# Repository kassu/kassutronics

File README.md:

# kassutronics
Under the label _kassutronics_ I create original circuits for modular musical synthesizers and other do-it-yourself sound electronics projects. Some of these are available for sale as printed circuit boards and face plates, others are only circuits or instructions.

This repository contains build documentation for modules that are for sale, and some smaller projects/workshops that are available as open source material.

## See also
- [Kassutronics blog](https://kassu2000.blogspot.com)
- [Kassutronics store](https://store.kassutronics.net)

- Added a new line just for testing the collaborative feature

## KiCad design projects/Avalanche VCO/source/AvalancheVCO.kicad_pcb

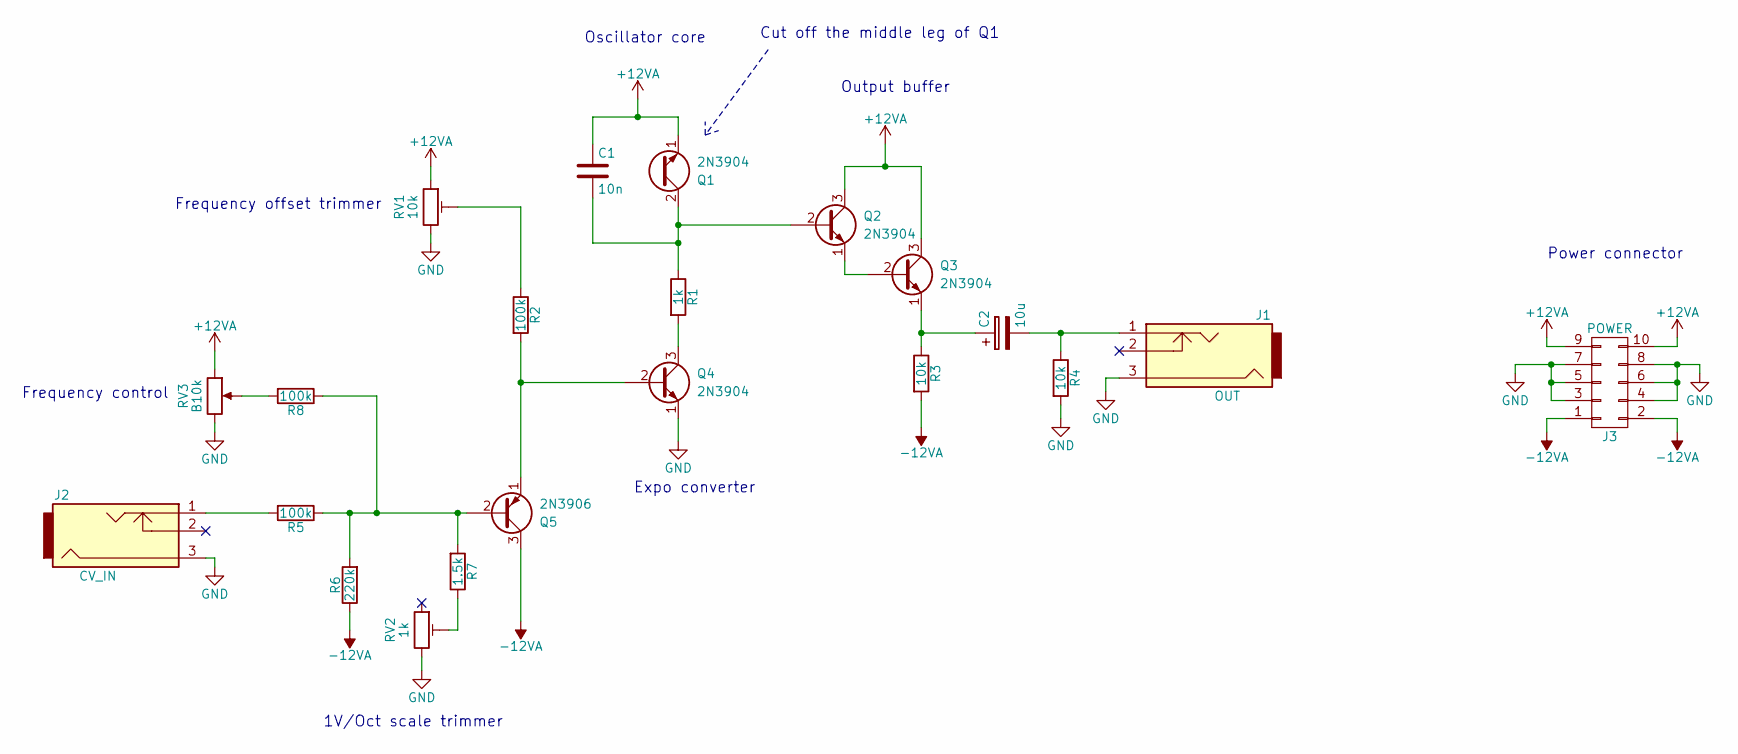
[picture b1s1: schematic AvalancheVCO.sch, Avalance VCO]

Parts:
C1: 10n; C_Rect_L7.2mm_W2.5mm_P5.00mm_FKS2_FKP2_MKS2_MKP2
C2: 10u; CP_Radial_D6.3mm_P2.50mm
J1: OUT; Thonkiconn
J2: CV_IN; Thonkiconn
J3: POWER; Pin_Header_Angled_2x05_Pitch2.54mm
Q1: 2N3904; TO-92-2pin_Inline_Wide
Q2, Q3, Q4: 2N3904; TO-92_Inline_Wide
Q5: 2N3906; TO-92_Inline_Wide
R1: 1k; R_Axial_DIN0204_L3.6mm_D1.6mm_P7.62mm_Horizontal
R2: 100k; R_Axial_DIN0204_L3.6mm_D1.6mm_P2.54mm_Vertical
R3: 10k; R_Axial_DIN0207_L6.3mm_D2.5mm_P15.24mm_Horizontal
R4: 10k; R_Axial_DIN0204_L3.6mm_D1.6mm_P7.62mm_Horizontal
R5, R8: 100k; R_Axial_DIN0204_L3.6mm_D1.6mm_P7.62mm_Horizontal
R6: 220k; R_Axial_DIN0204_L3.6mm_D1.6mm_P2.54mm_Vertical
R7: 1.5k; R_Axial_DIN0204_L3.6mm_D1.6mm_P5.08mm_Horizontal
RV1: 10k; Potentiometer_Trimmer_Bourns_3296X
RV2: 1k; Potentiometer_Trimmer_Bourns_3296X
RV3: B10k; Potentiometer_Alps_RK09K_Horizontal_ProtoBoard_Kassu

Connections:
+12VA: C1.1, J3.9, J3.10, Q1.1 (E), Q2.3 (C), Q3.3 (C), RV1.1, RV3.1
-12VA: J3.1, J3.2, Q5.3 (C), R3.2, R6.1
GND: J1.3, J2.3, J3.3, J3.4, J3.5, J3.6, J3.7, J3.8, Q4.1 (E), R4.2, RV1.3, RV2.3, RV3.3
unnamed: C1.2, Q1.2 (C), Q2.2 (B), R1.1
unnamed: C2.1, Q3.1 (E), R3.1
unnamed: C2.2, J1.1, R4.1
unnamed: J2.1, R5.2
unnamed: Q2.1 (E), Q3.2 (B)
unnamed: Q4.2 (B), Q5.1 (E), R2.2
unnamed: Q4.3 (C), R1.2
unnamed: Q5.2 (B), R5.1, R6.2, R7.2, R8.1
unnamed: R2.1, RV1.2
unnamed: R7.1, RV2.2
unnamed: R8.2, RV3.2

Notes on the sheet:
Frequency control
1V/Oct scale trimmer
Frequency offset trimmer
Oscillator core
Expo converter
Output buffer
Cut off the middle leg of Q1
Power connector

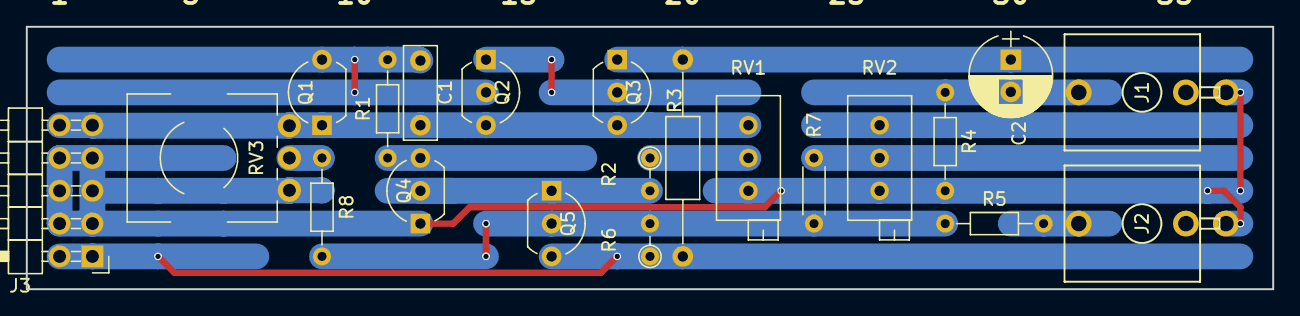
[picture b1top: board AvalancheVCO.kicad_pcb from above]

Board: 2 copper layers, 96.5 x 20.3 mm, 21 parts (0 on the bottom side), 14 nets.

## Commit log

2020-05-01 Create Instructions
2020-05-01 Rename Instructions to Programming using an Arduino Uno.md
2020-10-08 Add Slope 2.0A documentation
2021-11-30 Add Wavefolder 1.0 documentation
2023-09-09 Rename for consistency
2023-09-13 Create Quantizer_Build_Docs_1.2A.pdf
    Add build documentation for PCB revision 1.2

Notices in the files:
projects/Avalanche VCO/source/AvalancheVCO.sch:
(C) 2018 Caspar Ockeloen-Korppi
